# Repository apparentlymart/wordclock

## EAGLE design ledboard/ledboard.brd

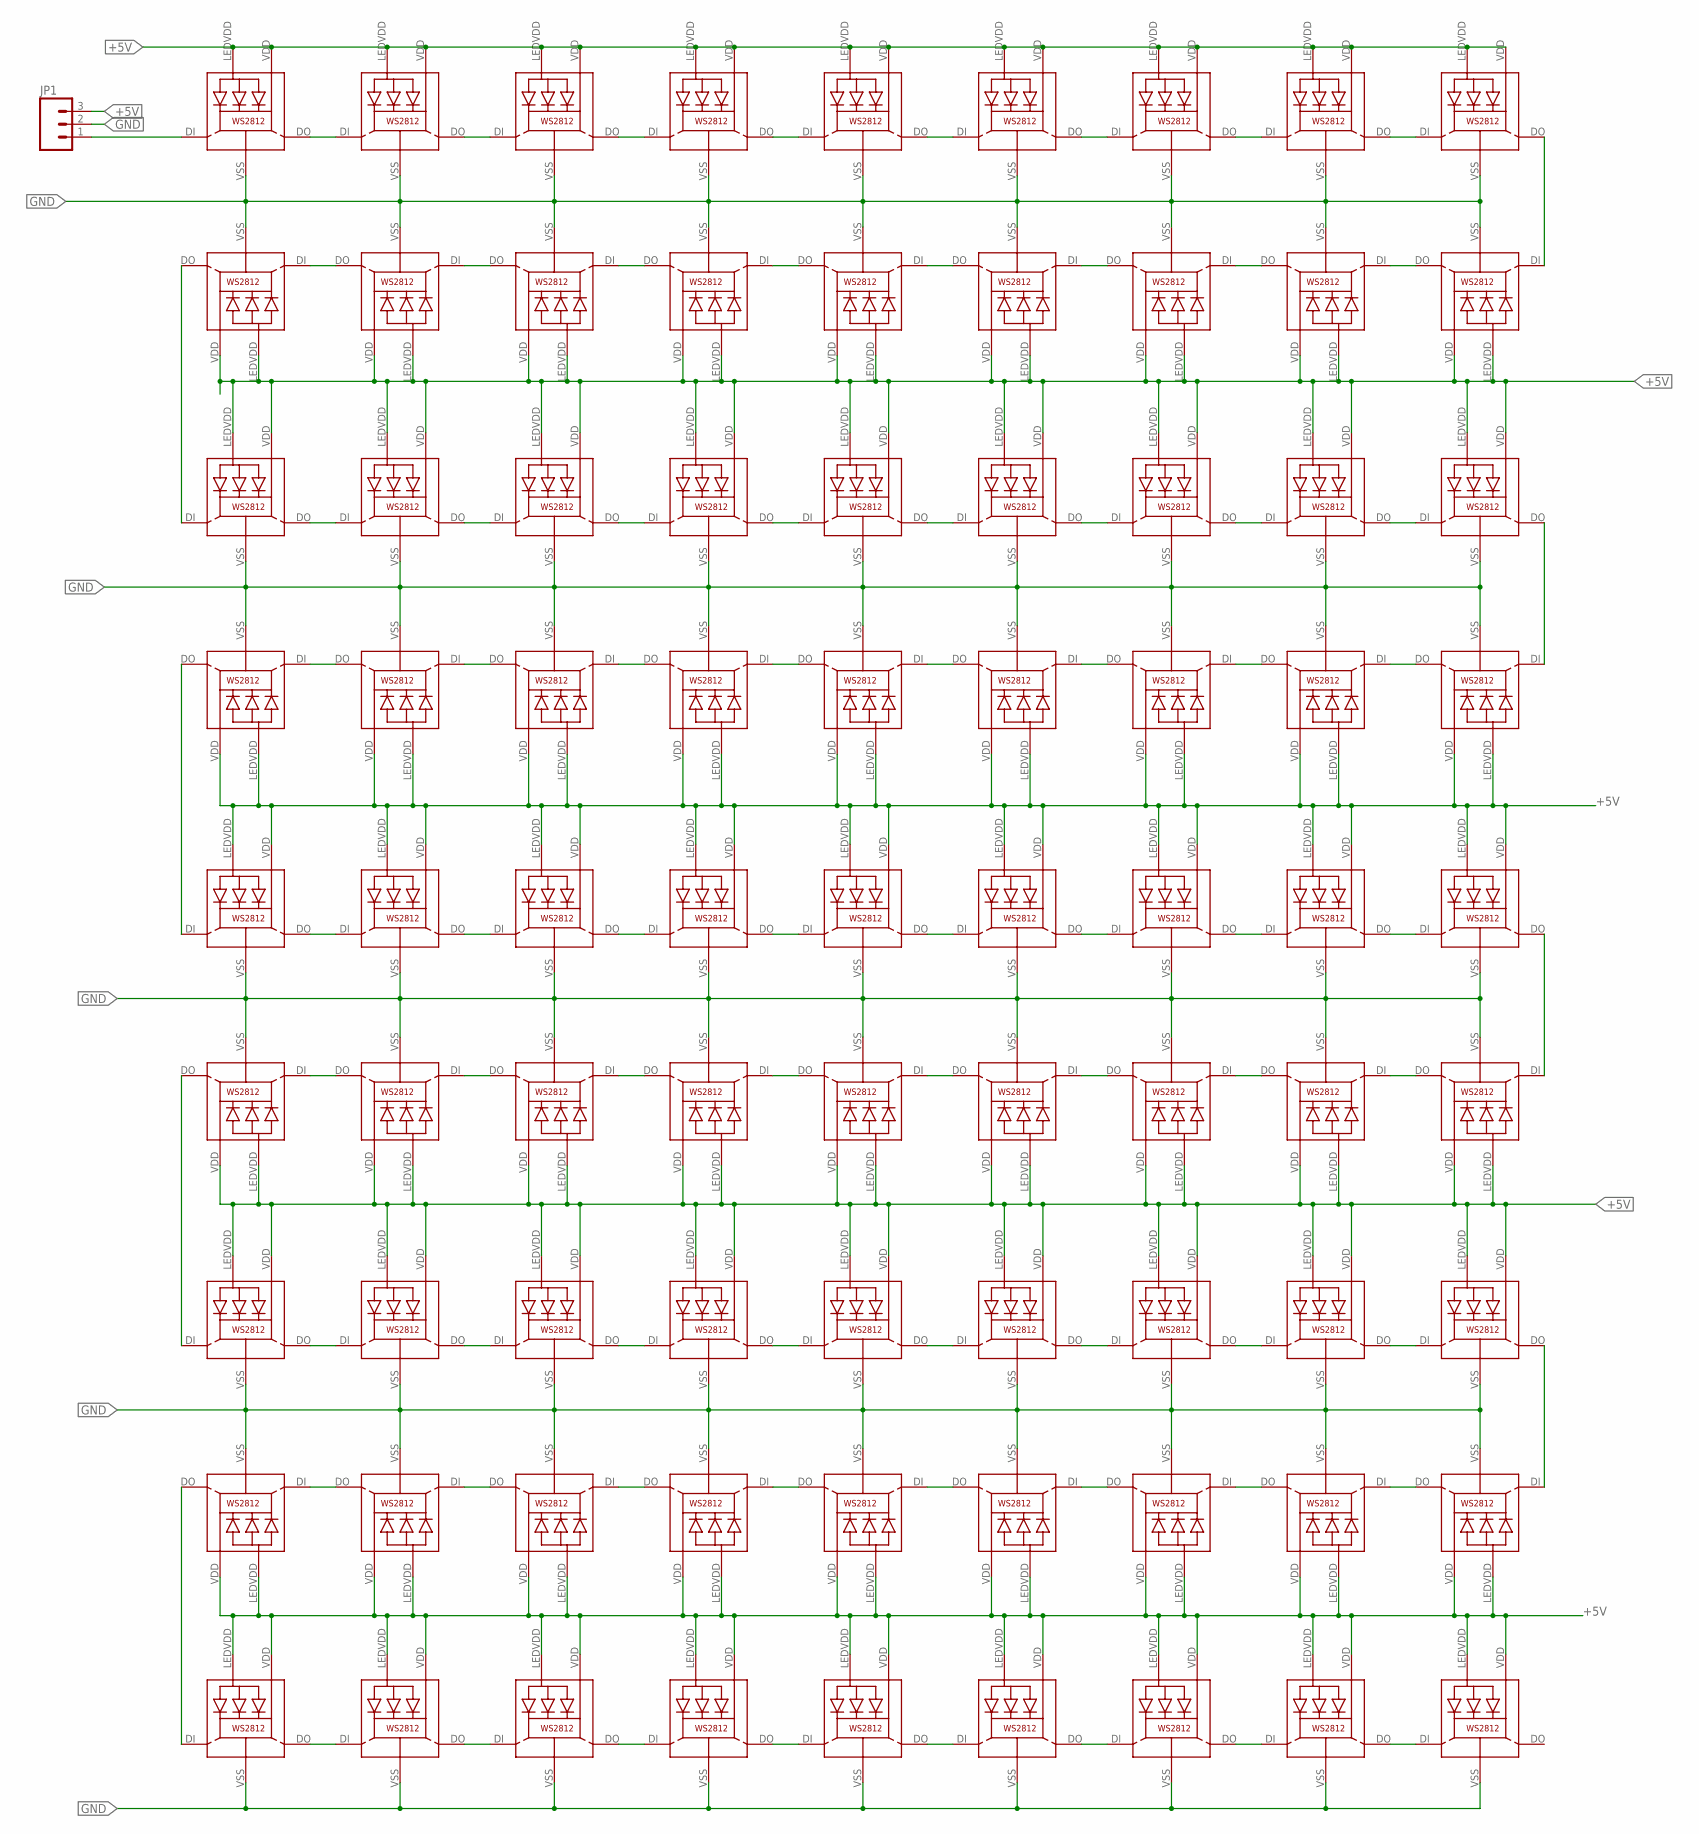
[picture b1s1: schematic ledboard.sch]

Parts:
JP1: M03LONGPADS; 1X03_LONGPADS
LEDG00, LEDG01, LEDG02, LEDG03, LEDG04, LEDG05, LEDG06, LEDG07, LEDG08, LEDG10, LEDG11, LEDG12, LEDG13, LEDG14, LEDG15, LEDG16, LEDG17, LEDG18, LEDG20, LEDG21, LEDG22, LEDG23, LEDG24, LEDG25, LEDG26, LEDG27, LEDG28, LEDG30, LEDG31, LEDG32, LEDG33, LEDG34, LEDG35, LEDG36, LEDG37, LEDG38, LEDG40, LEDG41, LEDG42, LEDG43, LEDG44, LEDG45, LEDG46, LEDG47, LEDG48, LEDG50, LEDG51, LEDG52, LEDG53, LEDG54, LEDG55, LEDG56, LEDG57, LEDG58, LEDG60, LEDG61, LEDG62, LEDG63, LEDG64, LEDG65, LEDG66, LEDG67, LEDG68, LEDG70, LEDG71, LEDG72, LEDG73, LEDG74, LEDG75, LEDG76, LEDG77, LEDG78, LEDG80, LEDG81, LEDG82, LEDG83, LEDG84, LEDG85, LEDG86, LEDG87, LEDG88: WS2812

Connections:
+5V: JP1.3, LEDG00.LEDVDD, LEDG00.VDD, LEDG01.LEDVDD, LEDG01.VDD, LEDG02.LEDVDD, LEDG02.VDD, LEDG03.LEDVDD, LEDG03.VDD, LEDG04.LEDVDD, LEDG04.VDD, LEDG05.LEDVDD, LEDG05.VDD, LEDG06.LEDVDD, LEDG06.VDD, LEDG07.LEDVDD, LEDG07.VDD, LEDG08.LEDVDD, LEDG08.VDD, LEDG10.LEDVDD, LEDG10.VDD, LEDG11.LEDVDD, LEDG11.VDD, LEDG12.LEDVDD, LEDG12.VDD, LEDG13.LEDVDD, LEDG13.VDD, LEDG14.LEDVDD, LEDG14.VDD, LEDG15.LEDVDD, LEDG15.VDD, LEDG16.LEDVDD, LEDG16.VDD, LEDG17.LEDVDD, LEDG17.VDD, LEDG18.LEDVDD, LEDG18.VDD, LEDG20.LEDVDD, LEDG20.VDD, LEDG21.LEDVDD, LEDG21.VDD, LEDG22.LEDVDD, LEDG22.VDD, LEDG23.LEDVDD, LEDG23.VDD, LEDG24.LEDVDD, LEDG24.VDD, LEDG25.LEDVDD, LEDG25.VDD, LEDG26.LEDVDD, LEDG26.VDD, LEDG27.LEDVDD, LEDG27.VDD, LEDG28.LEDVDD, LEDG28.VDD, LEDG30.LEDVDD, LEDG30.VDD, LEDG31.LEDVDD, LEDG31.VDD, LEDG32.LEDVDD, LEDG32.VDD, LEDG33.LEDVDD, LEDG33.VDD, LEDG34.LEDVDD, LEDG34.VDD, LEDG35.LEDVDD, LEDG35.VDD, LEDG36.LEDVDD, LEDG36.VDD, LEDG37.LEDVDD, LEDG37.VDD, LEDG38.LEDVDD, LEDG38.VDD, LEDG40.LEDVDD, LEDG40.VDD, LEDG41.LEDVDD, LEDG41.VDD, LEDG42.LEDVDD, LEDG42.VDD, LEDG43.LEDVDD, LEDG43.VDD, LEDG44.LEDVDD, LEDG44.VDD, LEDG45.LEDVDD, LEDG45.VDD, LEDG46.LEDVDD, LEDG46.VDD, LEDG47.LEDVDD, LEDG47.VDD, LEDG48.LEDVDD, LEDG48.VDD, LEDG50.LEDVDD, LEDG50.VDD, LEDG51.LEDVDD, LEDG51.VDD, LEDG52.LEDVDD, LEDG52.VDD, LEDG53.LEDVDD, LEDG53.VDD, LEDG54.LEDVDD, LEDG54.VDD, LEDG55.LEDVDD, LEDG55.VDD, LEDG56.LEDVDD, LEDG56.VDD, LEDG57.LEDVDD, LEDG57.VDD, LEDG58.LEDVDD, LEDG58.VDD, LEDG60.LEDVDD, LEDG60.VDD, LEDG61.LEDVDD, LEDG61.VDD, LEDG62.LEDVDD, LEDG62.VDD, LEDG63.LEDVDD, LEDG63.VDD, LEDG64.LEDVDD, LEDG64.VDD, LEDG65.LEDVDD, LEDG65.VDD, LEDG66.LEDVDD, LEDG66.VDD, LEDG67.LEDVDD, LEDG67.VDD, LEDG68.LEDVDD, LEDG68.VDD, LEDG70.LEDVDD, LEDG70.VDD, LEDG71.LEDVDD, LEDG71.VDD, LEDG72.LEDVDD, LEDG72.VDD, LEDG73.LEDVDD, LEDG73.VDD, LEDG74.LEDVDD, LEDG74.VDD, LEDG75.LEDVDD, LEDG75.VDD, LEDG76.LEDVDD, LEDG76.VDD, LEDG77.LEDVDD, LEDG77.VDD, LEDG78.LEDVDD, LEDG78.VDD, LEDG80.LEDVDD, LEDG80.VDD, LEDG81.LEDVDD, LEDG81.VDD, LEDG82.LEDVDD, LEDG82.VDD, LEDG83.LEDVDD, LEDG83.VDD, LEDG84.LEDVDD, LEDG84.VDD, LEDG85.LEDVDD, LEDG85.VDD, LEDG86.LEDVDD, LEDG86.VDD, LEDG87.LEDVDD, LEDG87.VDD, LEDG88.LEDVDD, LEDG88.VDD
DIN: JP1.1, LEDG00.DI
GND: JP1.2, LEDG00.VSS (GND), LEDG01.VSS (GND), LEDG02.VSS (GND), LEDG03.VSS (GND), LEDG04.VSS (GND), LEDG05.VSS (GND), LEDG06.VSS (GND), LEDG07.VSS (GND), LEDG08.VSS (GND), LEDG10.VSS (GND), LEDG11.VSS (GND), LEDG12.VSS (GND), LEDG13.VSS (GND), LEDG14.VSS (GND), LEDG15.VSS (GND), LEDG16.VSS (GND), LEDG17.VSS (GND), LEDG18.VSS (GND), LEDG20.VSS (GND), LEDG21.VSS (GND), LEDG22.VSS (GND), LEDG23.VSS (GND), LEDG24.VSS (GND), LEDG25.VSS (GND), LEDG26.VSS (GND), LEDG27.VSS (GND), LEDG28.VSS (GND), LEDG30.VSS (GND), LEDG31.VSS (GND), LEDG32.VSS (GND), LEDG33.VSS (GND), LEDG34.VSS (GND), LEDG35.VSS (GND), LEDG36.VSS (GND), LEDG37.VSS (GND), LEDG38.VSS (GND), LEDG40.VSS (GND), LEDG41.VSS (GND), LEDG42.VSS (GND), LEDG43.VSS (GND), LEDG44.VSS (GND), LEDG45.VSS (GND), LEDG46.VSS (GND), LEDG47.VSS (GND), LEDG48.VSS (GND), LEDG50.VSS (GND), LEDG51.VSS (GND), LEDG52.VSS (GND), LEDG53.VSS (GND), LEDG54.VSS (GND), LEDG55.VSS (GND), LEDG56.VSS (GND), LEDG57.VSS (GND), LEDG58.VSS (GND), LEDG60.VSS (GND), LEDG61.VSS (GND), LEDG62.VSS (GND), LEDG63.VSS (GND), LEDG64.VSS (GND), LEDG65.VSS (GND), LEDG66.VSS (GND), LEDG67.VSS (GND), LEDG68.VSS (GND), LEDG70.VSS (GND), LEDG71.VSS (GND), LEDG72.VSS (GND), LEDG73.VSS (GND), LEDG74.VSS (GND), LEDG75.VSS (GND), LEDG76.VSS (GND), LEDG77.VSS (GND), LEDG78.VSS (GND), LEDG80.VSS (GND), LEDG81.VSS (GND), LEDG82.VSS (GND), LEDG83.VSS (GND), LEDG84.VSS (GND), LEDG85.VSS (GND), LEDG86.VSS (GND), LEDG87.VSS (GND), LEDG88.VSS (GND)
unnamed: LEDG00.DO, LEDG10.DI
unnamed: LEDG10.DO, LEDG20.DI
unnamed: LEDG20.DO, LEDG30.DI
unnamed: LEDG30.DO, LEDG40.DI
unnamed: LEDG40.DO, LEDG50.DI
unnamed: LEDG50.DO, LEDG60.DI
unnamed: LEDG60.DO, LEDG70.DI
unnamed: LEDG70.DO, LEDG80.DI
unnamed: LEDG80.DO, LEDG81.DI
unnamed: LEDG71.DI, LEDG81.DO
unnamed: LEDG61.DI, LEDG71.DO
unnamed: LEDG51.DI, LEDG61.DO
unnamed: LEDG41.DI, LEDG51.DO
unnamed: LEDG31.DI, LEDG41.DO
unnamed: LEDG21.DI, LEDG31.DO
unnamed: LEDG11.DI, LEDG21.DO
unnamed: LEDG01.DI, LEDG11.DO
unnamed: LEDG01.DO, LEDG02.DI
unnamed: LEDG02.DO, LEDG12.DI
unnamed: LEDG12.DO, LEDG22.DI
unnamed: LEDG22.DO, LEDG32.DI
unnamed: LEDG32.DO, LEDG42.DI
unnamed: LEDG42.DO, LEDG52.DI
unnamed: LEDG52.DO, LEDG62.DI
unnamed: LEDG62.DO, LEDG72.DI
unnamed: LEDG72.DO, LEDG82.DI
unnamed: LEDG82.DO, LEDG83.DI
unnamed: LEDG73.DI, LEDG83.DO
unnamed: LEDG63.DI, LEDG73.DO
unnamed: LEDG53.DI, LEDG63.DO
unnamed: LEDG43.DI, LEDG53.DO
unnamed: LEDG33.DI, LEDG43.DO
unnamed: LEDG23.DI, LEDG33.DO
unnamed: LEDG13.DI, LEDG23.DO
unnamed: LEDG03.DI, LEDG13.DO
unnamed: LEDG03.DO, LEDG04.DI
unnamed: LEDG04.DO, LEDG14.DI
unnamed: LEDG14.DO, LEDG24.DI
unnamed: LEDG24.DO, LEDG34.DI
unnamed: LEDG34.DO, LEDG44.DI
unnamed: LEDG44.DO, LEDG54.DI
unnamed: LEDG54.DO, LEDG64.DI
unnamed: LEDG64.DO, LEDG74.DI
unnamed: LEDG74.DO, LEDG84.DI
unnamed: LEDG84.DO, LEDG85.DI
unnamed: LEDG75.DI, LEDG85.DO
unnamed: LEDG65.DI, LEDG75.DO
unnamed: LEDG55.DI, LEDG65.DO
unnamed: LEDG45.DI, LEDG55.DO
unnamed: LEDG35.DI, LEDG45.DO
unnamed: LEDG25.DI, LEDG35.DO
unnamed: LEDG15.DI, LEDG25.DO
unnamed: LEDG05.DI, LEDG15.DO
unnamed: LEDG05.DO, LEDG06.DI
unnamed: LEDG06.DO, LEDG16.DI
unnamed: LEDG16.DO, LEDG26.DI
unnamed: LEDG26.DO, LEDG36.DI
unnamed: LEDG36.DO, LEDG46.DI
unnamed: LEDG46.DO, LEDG56.DI
unnamed: LEDG56.DO, LEDG66.DI
unnamed: LEDG66.DO, LEDG76.DI
unnamed: LEDG76.DO, LEDG86.DI
unnamed: LEDG86.DO, LEDG87.DI
unnamed: LEDG77.DI, LEDG87.DO
unnamed: LEDG67.DI, LEDG77.DO
unnamed: LEDG57.DI, LEDG67.DO
unnamed: LEDG47.DI, LEDG57.DO
unnamed: LEDG37.DI, LEDG47.DO
unnamed: LEDG27.DI, LEDG37.DO
unnamed: LEDG17.DI, LEDG27.DO
unnamed: LEDG07.DI, LEDG17.DO
unnamed: LEDG07.DO, LEDG08.DI
unnamed: LEDG08.DO, LEDG18.DI
unnamed: LEDG18.DO, LEDG28.DI
unnamed: LEDG28.DO, LEDG38.DI
unnamed: LEDG38.DO, LEDG48.DI
unnamed: LEDG48.DO, LEDG58.DI
unnamed: LEDG58.DO, LEDG68.DI
unnamed: LEDG68.DO, LEDG78.DI
unnamed: LEDG78.DO, LEDG88.DI

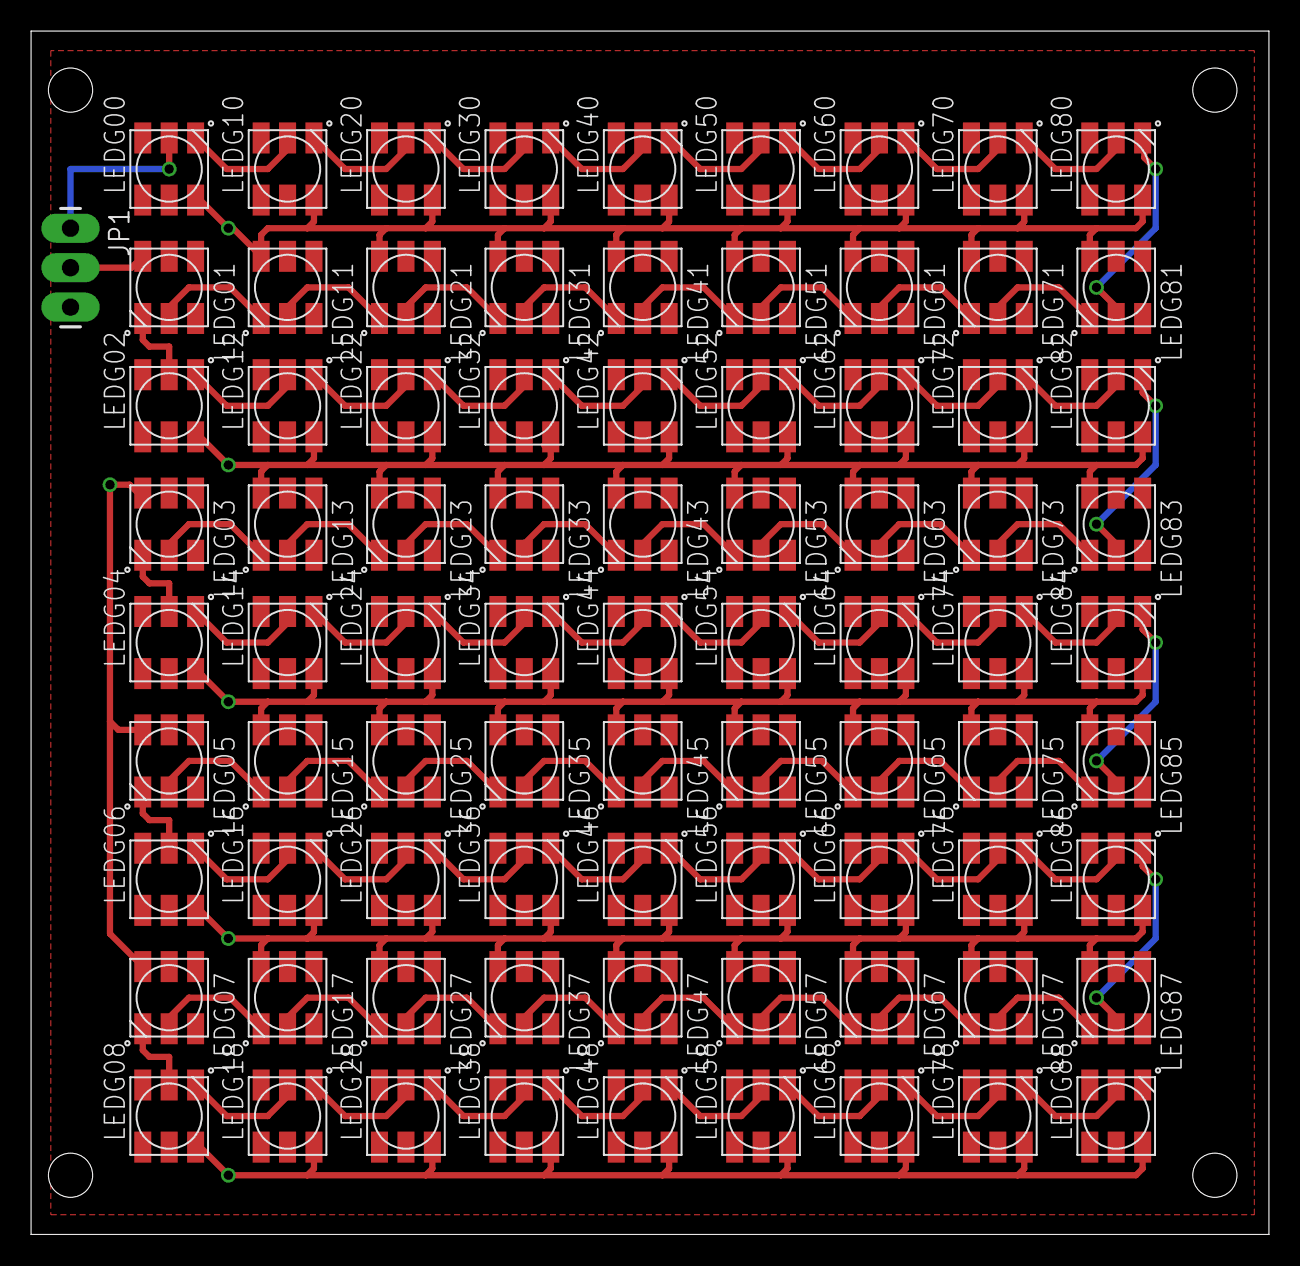
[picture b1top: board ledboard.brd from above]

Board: 2 copper layers, 79.7 x 77.5 mm, 82 parts (0 on the bottom side), 83 nets.

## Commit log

2013-09-14 prototyping.
    The major failing of this prototype is that I forgot to include "TWELVE"
    in the word matrix, so the next iteration of this will require some
    changes in that regard.
2013-09-15 Better prototype which can actually say TWELVE.
    Got rid of the "IT IS" words; they're not very interesting anyway since
    they are just always illuminated. We can still say
    TIME TO EAT / SLEEP / GO / WAKE UP as well as actual time readouts.
2013-09-15 Hacked up script to make an SVG of the letters to print.
    What it generates is not quite aligned properly so it needs some manual
    post-processing before printing.
2013-09-16 Notes about a config that takes only 9x9 LEDs
2013-12-08 PCB design for a 9x9 "neopixel" board.
2014-04-14 Add some notes about wordclocks in other languages.
    Summary: looks like 9x9 is a sweet spot for English, but not for French,
    German or Spanish. Would need to grow a bit to support other languages
    on the same hardware. Not tried 10x10 yet, but we know that ended up
    a little *too* spacious for English.
2014-04-14 Expanding to 10x10 makes it work for French, German and Spanish too.
    No such luck with Latin or Russian, since the related vocabulary there
    doesn't have many words that can overlap to save space.
2014-12-01 Two new design files for the latest iteration of the design.
2015-07-06 New PCB for a NeoPixel matrix.
2015-07-06 Move the board bits into the diagram borders.
2015-07-06 Edge cuts
2015-07-06 Final tweaks before ordering v0.1 PCBs.
2015-09-07 Increase NeoPixel hole sizes and add bigger capacitor.
2015-09-07 Add filled zones.
    These aren't really serving any electrical purpose, but since these boards
    are being manufactured very thin they are quite translucent where no
    copper is present.
2015-09-07 Bump revision to v0.2.
2015-09-07 Tweak the pad sizes on the Neopixel footprints.
    Making them a little narrower but a lot taller should make them less
    likely to short while easier to solder.
2015-09-07 SMD polarized capacitor footprint.
2015-09-07 More hole/pad tweaking for the NeoPixels.
    The tolerances here are pretty tight, but this now just about satisfies
    the design rules at Seeedstudio.

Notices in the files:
parts and their libraries:
SparkFun-Connectors: Licensing: CC v3.0 Share-Alike You are welcome to use this library for commercial purposes.
